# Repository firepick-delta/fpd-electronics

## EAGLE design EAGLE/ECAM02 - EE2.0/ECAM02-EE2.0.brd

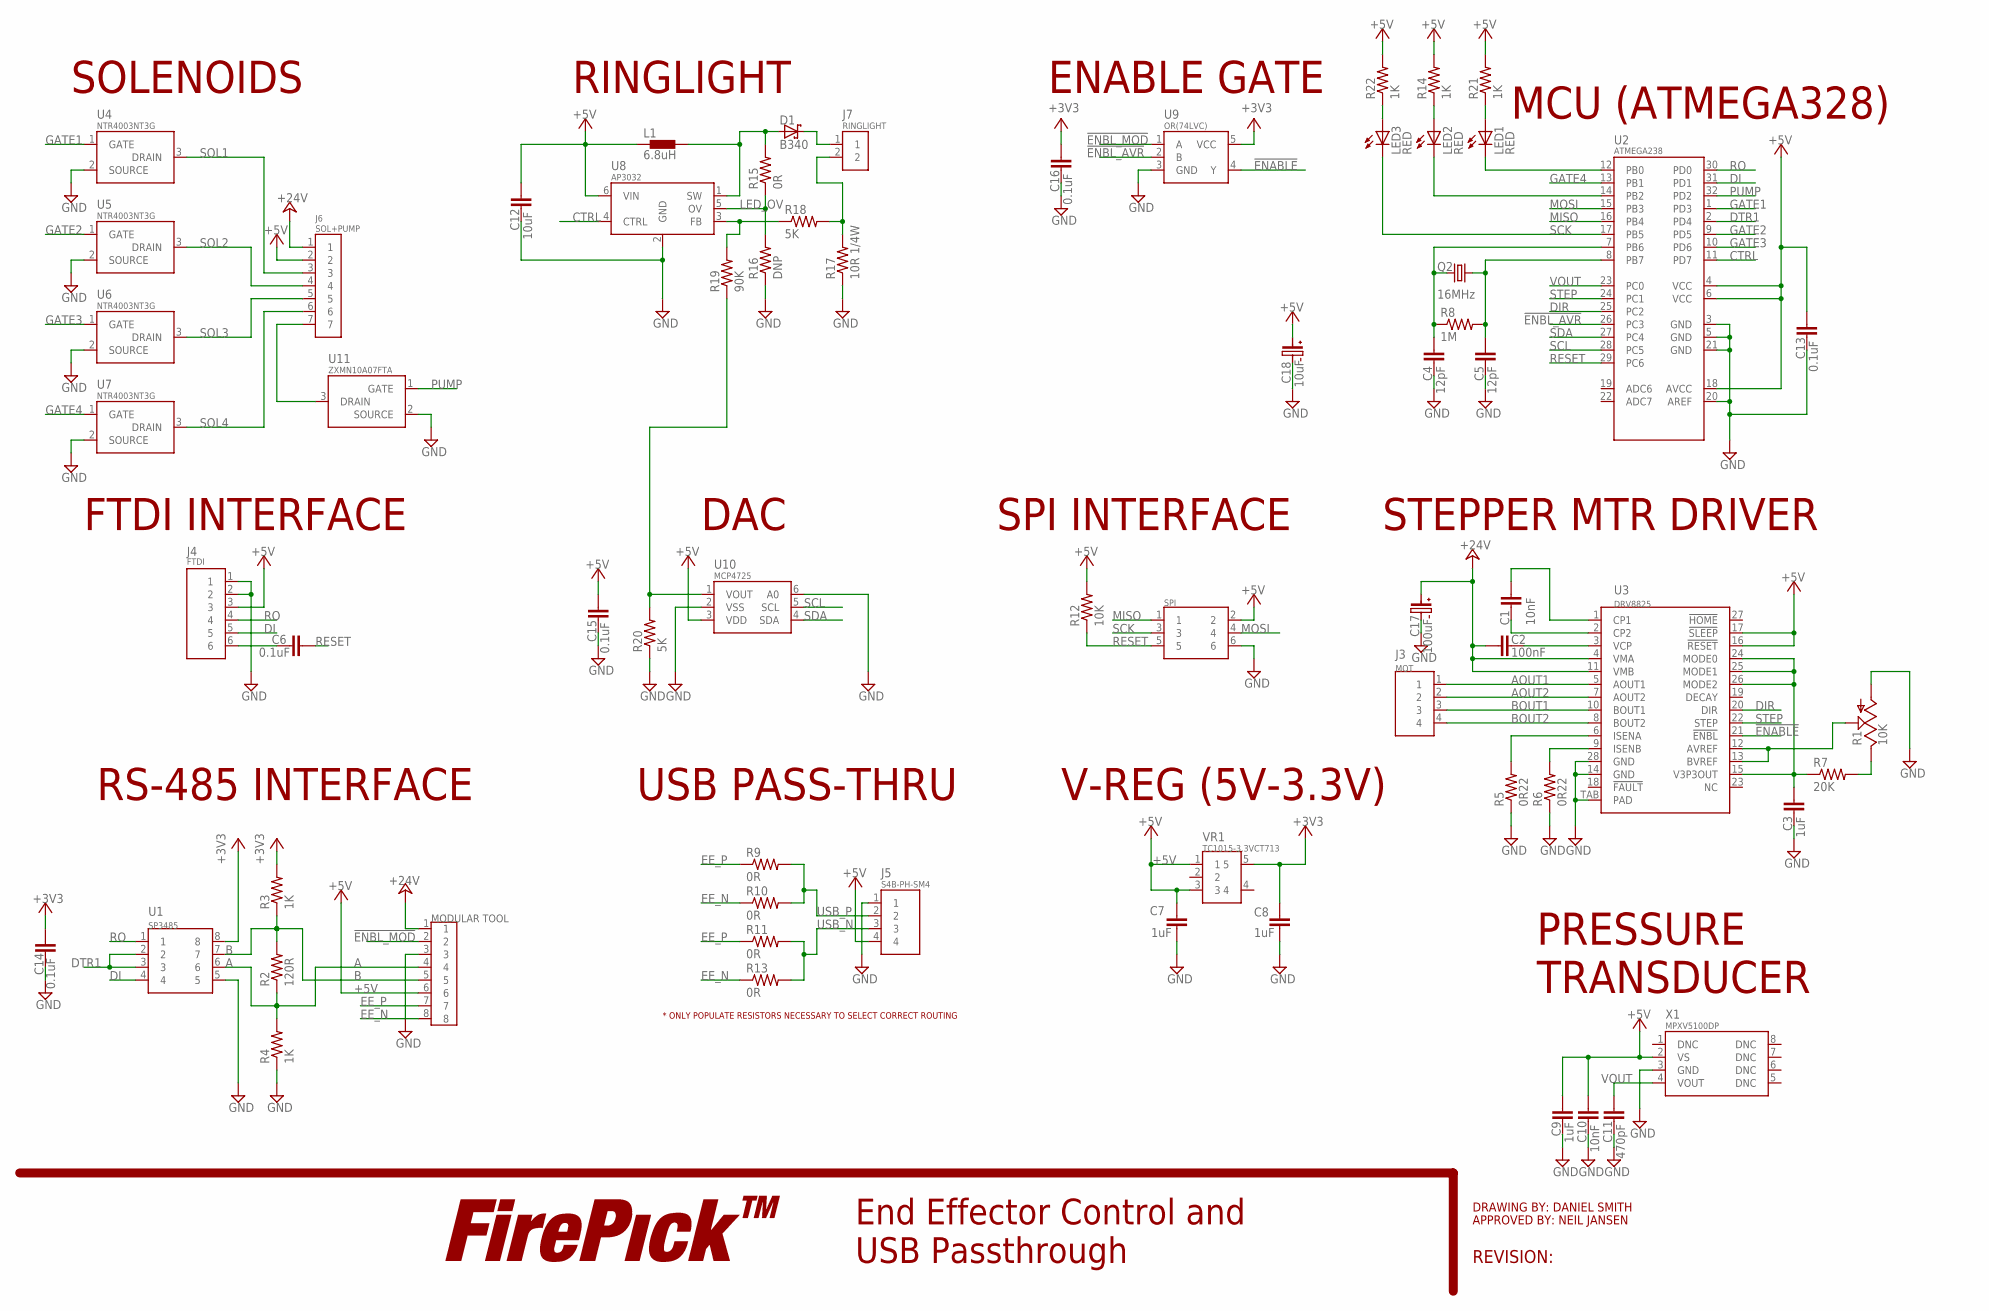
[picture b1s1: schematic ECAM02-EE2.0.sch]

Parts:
C1, C10: 10nF; C0603; PARTNO GRM188R71H103KA01D
C2: 100nF; C0603; PARTNO UMK107B7104KA-T
C3, C7, C8, C9: 1uF; C0603; PARTNO UMK107AB7105KA-T
C4, C5: 12pF; C0603; PARTNO GRM1885C1H120FA01J
C6: 0.1uF; C0603; PARTNO UMK107B7104KA-T
C11: 470pF; C0603; PARTNO GRM188R72A471KA01D
C12: 10uF; C0603; PARTNO GRM188R61C106MA73D
C13, C14, C15, C16: 0.1uF; C0603; PARTNO GMK107BJ104KAHT
C17: 100uF; C-SMD-6.3MM; PARTNO EMVA500ADA101MHA0G
C18: 10uF; C-SMD-6.3MM; PARTNO EMVH350ADA100MF60G
D1: B340; DIO-SMA; PARTNO B340A-13-F
J1: MODULAR TOOL; CON-JST-PH-2.0MM-8P-SMT-VRT; PARTNO B8B-PH-SM4-TB(LF)(SN)
J2: SPI; CON-HDR-2X3P; PARTNO 67996-206HLF
J3: MOT; CON-JST-PH-2.0MM-4P-THRU-VRT; PARTNO B4B-PH-K-S(LF)(SN)
J4: FTDI; CON-HDR-6POS-MALE; PARTNO S6B-PH-SM4-TB(LF)(SN)
J5: S4B-PH-SM4; CON-JST-PH-2.0MM-4P-SMT-VRT; PARTNO S4B-PH-SM4-TB(LF)(SN)
J6: SOL+PUMP; CON-JST-PH-2.0MM-7P-SMT-VRT; PARTNO B7B-PH-SM4-TB(LF)(SN)
J7: RINGLIGHT; CON-JST-PH-2.0MM-2P-SMT-VRT; PARTNO B2B-PH-SM4-TB(LF)(SN)
L1: 6.8uH; 0603; PARTNO BRL1608T6R8M
LED1, LED2, LED3: RED; LED0603
LOGO2: LOGO-FIREPICKLARGE; LOGO-FIREPICK
Q2: 16MHz; HC-49/U-S; PARTNO HCM4916000000ABJT
R1: 10K; TC33X-2; PARTNO TC33X-2-103E
R2: 120R; R0603; PARTNO RC0603FR-07120RL
R3, R4: 1K; R0603; PARTNO RC0603FR-071KL
R5, R6: 0R22; R1206; PARTNO RL1206FR-7W0R22L
R7: 20K; R0603; PARTNO RC0603FR-0722KL
R8: 1M; R0603; PARTNO RC0603FR-071ML
R9, R10, R11, R13, R15: 0R; R0603; PARTNO RC0603JR-070RL
R12: 10K; R0603; PARTNO RC0603FR-0710KL
R14, R21, R22: 1K; R0603
R16: DNP; R0603; PARTNO RC0603JR-070RL
R17: 10R 1/4W; R1206; PARTNO RC1206FR-0710RL
R18, R20: 5K; R0603; PARTNO PNM0603E5001BST5
R19: 90K; R0603; PARTNO RC0603FR-0790K9L
U1: SP3485; SOICN-8; PARTNO SP3485
U2: ATMEGA238; 32-TQF(ATMEGA); PARTNO ATMEGA328-AUR
U3: DRV8825; 28-HSSOP; PARTNO DRV8825PWPR
U4, U5, U6, U7: NTR4003NT3G; SOT-23-3; PARTNO NTR4003NT3G
U8: AP3032; SOT-23-6; PARTNO AP3032KTR-G1
U9: OR(74LVC); SOT-23-5; PARTNO SN74LVC1G32DBVR
U10: MCP4725; SOT-23-6; PARTNO MCP4725A0T-E/CH
U11: ZXMN10A07FTA; SOT-23-3; PARTNO ZXMN10A07FTA
VR1: TC1015-3.3VCT713; SOT-23-5; PARTNO TC1015-3.3VCT713
X1: MPXV5100DP; 8-SMD; PARTNO MPXV5100DP

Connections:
!ENABLE: U3.21 (!ENBL), U9.4 (Y)
!ENBL_AVR: U2.26 (PC3), U9.2 (B)
!ENBL_MOD: J1.2, U9.1 (A)
+3V3: C8.2, C14.2, C16.2, R3.2, U1.8, U9.5 (VCC), VR1.5
+5V: C7.2, C9.2, C10.2, C12.2, C13.2, C15.2, C18.POS, J1.6, J2.2, J4.3, J5.4, J6.2, L1.1, R12.2, R14.2, R21.2, R22.2, U2.4 (VCC), U2.6 (VCC), U2.18 (AVCC), U3.16 (!RESET), U3.17 (!SLEEP), U8.6 (VIN), U10.3 (VDD), VR1.1, VR1.3, X1.2 (VS)
+24V: C2.1, C17.POS, J1.1, J6.1, U3.4 (VMA), U3.11 (VMB)
A: J1.4, R2.1, R4.2, U1.6
AOUT1: J3.1, U3.5 (AOUT1)
AOUT2: J3.2, U3.7 (AOUT2)
B: J1.5, R2.2, R3.1, U1.7
BOUT1: J3.3, U3.10 (BOUT1)
BOUT2: J3.4, U3.8 (BOUT2)
CTRL: U2.11 (PD7), U8.4 (CTRL)
DI: J4.5, U1.4, U2.31 (PD1)
DIR: U2.25 (PC2), U3.20 (DIR)
DTR1: U1.2, U1.3, U2.2 (PD4)
EE_N: J1.8, R10.1, R13.1
EE_P: J1.7, R9.1, R11.1
GATE1: U2.1 (PD3), U4.1 (GATE)
GATE2: U2.9 (PD5), U5.1 (GATE)
GATE3: U2.10 (PD6), U6.1 (GATE)
GATE4: U2.13 (PB1), U7.1 (GATE)
GND: C3.1, C4.1, C5.1, C7.1, C8.1, C9.1, C10.1, C11.1, C12.1, C13.1, C14.1, C15.1, C16.1, C17.NEG, C18.NEG, J1.3, J2.6, J4.1, J4.2, J5.1, R1.1 (A), R4.1, R5.1, R6.1, R16.1, R17.1, R20.1, U1.5, U2.3 (GND), U2.5 (GND), U2.20 (AREF), U2.21 (GND), U3.14 (GND), U3.28 (GND), U3.TAB (PAD), U4.2 (SOURCE), U5.2 (SOURCE), U6.2 (SOURCE), U7.2 (SOURCE), U8.2 (GND), U9.3 (GND), U10.2 (VSS), U10.6 (A0), U11.2 (SOURCE), X1.3 (GND)
LED_ANODE: D1.NEG (C), J7.1
LED_CATHODE: J7.2, R17.2, R18.2
LED_FB: R18.1, R19.2, U8.3 (FB)
LED_OV: R15.1, R16.2, U8.5 (OV)
LED_SW: D1.POS (A), L1.2, R15.2, U8.1 (SW)
MISO: J2.1, U2.16 (PB4)
MOSI: J2.4, U2.15 (PB3)
unnamed: LED1.A, R21.1
unnamed: LED2.A, R14.1
unnamed: LED1.C, U2.12 (PB0)
unnamed: LED2.C, U2.14 (PB2)
unnamed: C1.2, U3.1 (CP1)
unnamed: C1.1, U3.2 (CP2)
unnamed: C2.2, U3.3 (VCP)
unnamed: R5.2, U3.6 (ISENA)
unnamed: R6.2, U3.9 (ISENB)
unnamed: R19.1, R20.2, U10.1 (VOUT)
unnamed: LED3.A, R22.1
unnamed: J6.7, U11.3 (DRAIN)
unnamed: C3.2, R7.1, U3.15 (V3P3OUT), U3.24 (MODE0), U3.25 (MODE1), U3.26 (MODE2)
unnamed: R1.3 (E), R7.2
unnamed: R1.2 (S), U3.12 (AVREF), U3.13 (BVREF)
unnamed: C6.1, J4.6
PUMP: U2.32 (PD2), U11.1 (GATE)
RESET: C6.2, J2.5, R12.1, U2.29 (PC6)
RO: J4.4, U1.1, U2.30 (PD0)
SCK: J2.3, LED3.C, U2.17 (PB5)
SCL: U2.28 (PC5), U10.5 (SCL)
SDA: U2.27 (PC4), U10.4 (SDA)
SOL1: J6.3, U4.3 (DRAIN)
SOL2: J6.4, U5.3 (DRAIN)
SOL3: J6.5, U6.3 (DRAIN)
SOL4: J6.6, U7.3 (DRAIN)
STEP: U2.24 (PC1), U3.22 (STEP)
USB_N: J5.3, R11.2, R13.2
USB_P: J5.2, R9.2, R10.2
VOUT: C11.2, U2.23 (PC0), X1.4 (VOUT)
XTAL1: C4.2, Q2.1, R8.1, U2.7 (PB6)
XTAL2: C5.2, Q2.2, R8.2, U2.8 (PB7)

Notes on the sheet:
End Effector Control and USB Passthrough
DRAWING BY: DANIEL SMITH
APPROVED BY: NEIL JANSEN
REVISION:
RS-485 INTERFACE
MCU (ATMEGA328)
V-REG (5V-3.3V)
FTDI INTERFACE
STEPPER MTR DRIVER
USB PASS-THRU
* ONLY POPULATE RESISTORS NECESSARY TO SELECT CORRECT ROUTING
PRESSURE TRANSDUCER
SOLENOIDS
RINGLIGHT
ENABLE GATE
DAC
SPI INTERFACE
SPI

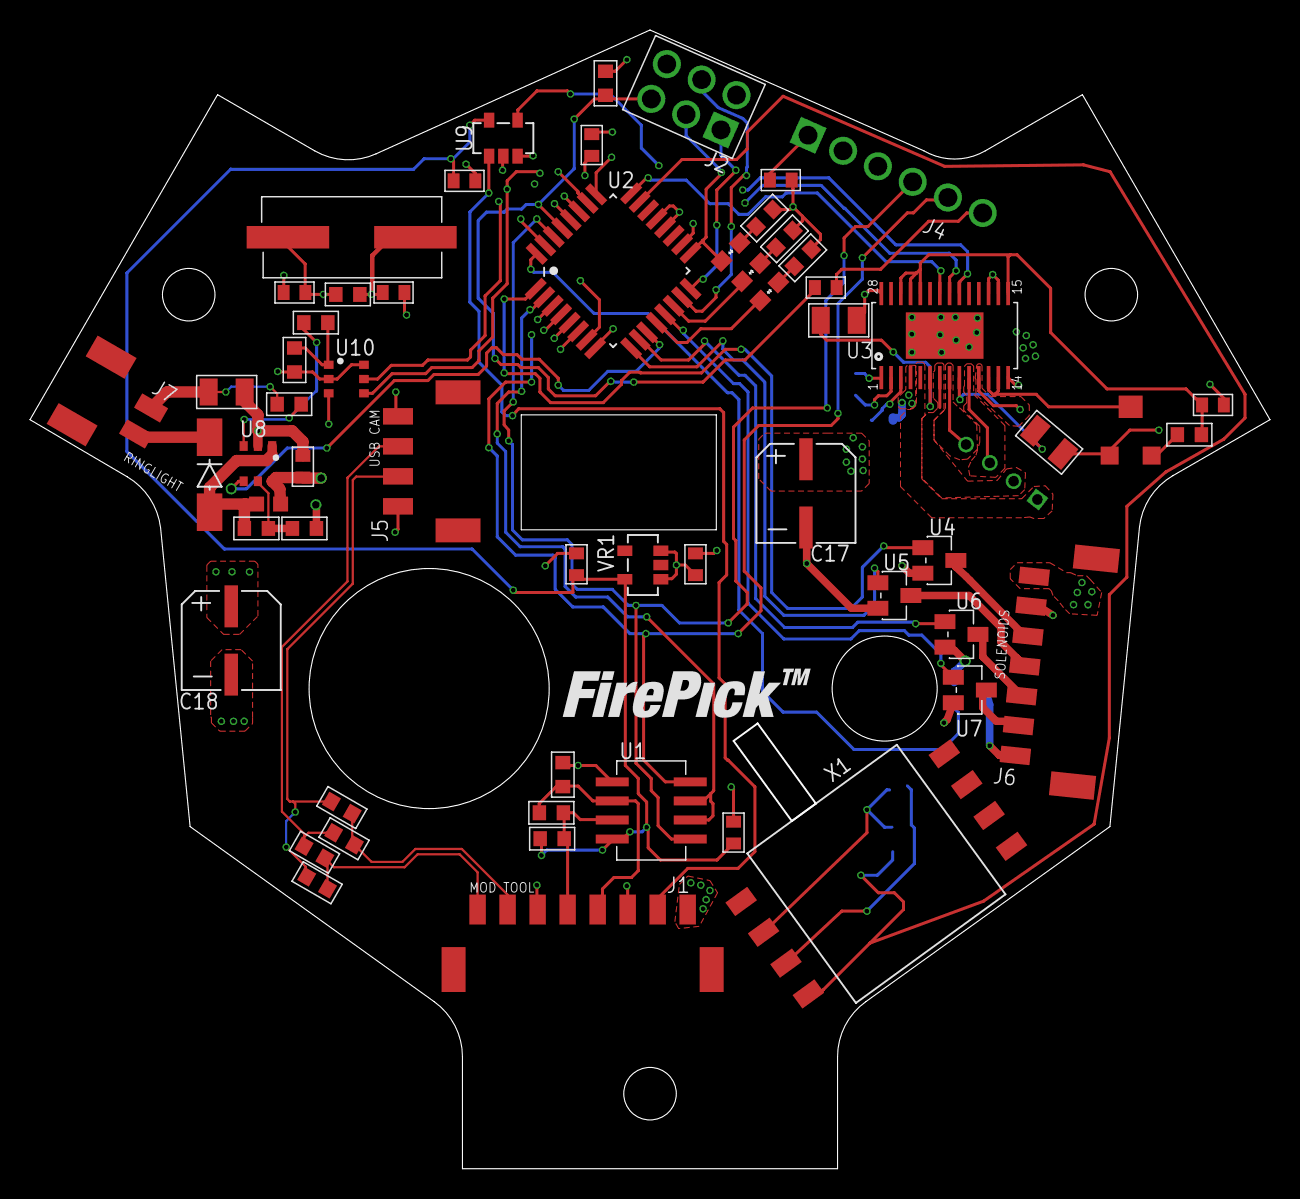
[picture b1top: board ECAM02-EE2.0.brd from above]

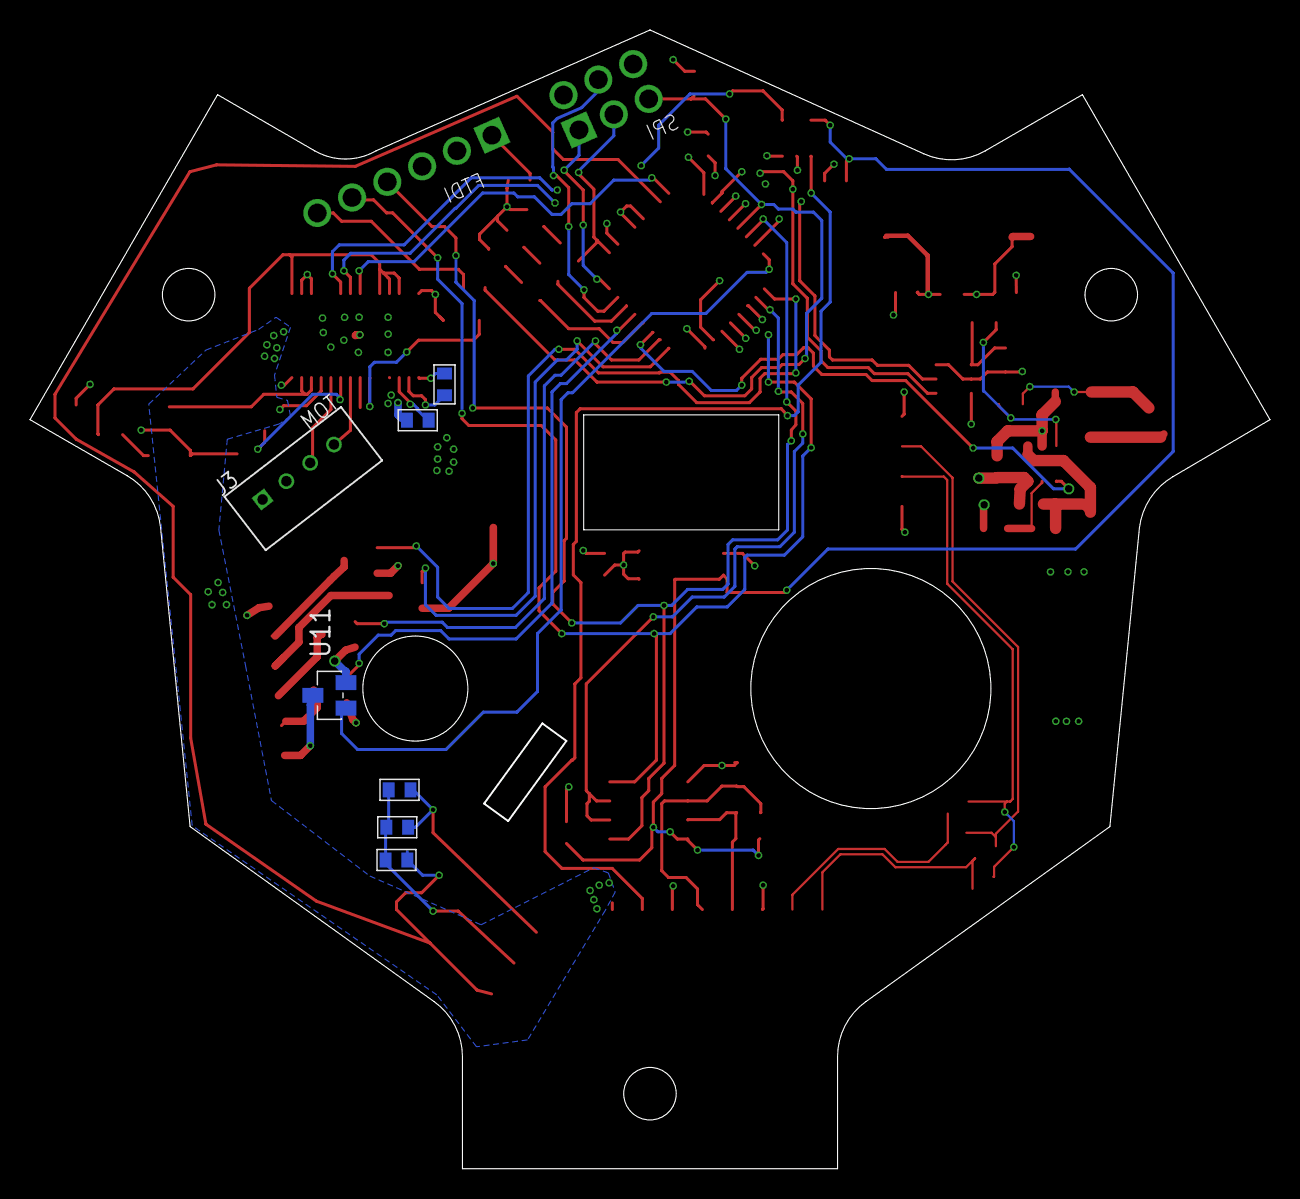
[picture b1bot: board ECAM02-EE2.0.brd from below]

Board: 4 copper layers, 82.5 x 75.8 mm, 67 parts (7 on the bottom side), 62 nets.

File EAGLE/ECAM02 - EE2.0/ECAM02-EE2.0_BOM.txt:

Mfg Part Num	Description	Qty-1	Part References	Price(USD):	Mfr:	Distr:	Digi-Key P/N:	Notes
ECAM02	End Effector & Downward Camera Board	-	ECAM02	-	Tin Whiskers Tech	-	-	
-	Bare PCB, FR-4, 0.062” Thickness	1	-		HQPCB	-	-	
GMK107BJ104KAHT	Capacitor: 0.1uF, 35V, 10%, X5R	4	C13, C14, C15, C16		Taiyo Yuden	ANY	587-3357-2-ND 	
UMK107B7104KA-T	Capacitor: 0.1uF, 50V, 10%, X7R	1	C6		Taiyo Yuden	ANY	587-1243-1-ND	
RC0603JR-070RL	Resistor: 0.0 Ohm, 0.1W, 0%	5	R9, R10, R11, R13, R15		Yageo	ANY	311-0.0GRCT-ND	
RL1206FR-7W0R22L	Resistor: 0.22 Ohm, 0.5W, 1%	2	R5, R6		Yageo	ANY	311-.22LYCT-ND	
RC0603FR-071KL	Resistor: 1 kOhm, 0.1W, 1%	2	R3, R4		Yageo	ANY	311-1.00KHRCT-ND	
RC0603FR-071ML	Resistor: 1 Mohm, 0.1W, 5%	1	R8		Yageo	ANY	311-1.00MHRCT-ND	
UMK107AB7105KA-T	Capacitor, 1uF, 50V, 10%	4	C3, C7, C8, C9		Taiyo Yuden	ANY	587-3247-1-ND	
PNM0603E5001BST5	Resistor: 5.0 kOhm, 0.1%, 0.15W	2	R18, R20		Vishay	ANY	PNM0603-5.0KBCT	
BRL1608T6R8M	Inductor: 6.8uH, 20%, SMT	1	L1		Taiyo Yuden	ANY	587-2902-1-ND	
RC0603FR-0710KL	Resistor: 10 kOhm, 0.1W, 1%	1	R12		Yageo	ANY	311-10.0KHRCT-ND	
TC33X-2-103E	Potentiometer: Trim, 10 kOhm, 0.1W, 25%	1	R1		Bourns Inc.	ANY	TC33X-103EDKR-ND	
RC1206FR-0710RL	Resistor: 10 Ohm, 0.25W, 1%	1	R17		Yageo	ANY	311-10.0FRCT-ND	
GRM188R71H103KA01D	Capacitor: 10nF, 50V, 10%, X7R	2	C1, C10		Murata	ANY	490-1512-1-ND	
EMVH350ADA100MF60G	Capacitor, AL-Electrolytic, 10uF, 35V, 20%	1	C18		United Chemi-Con	ANY	565-2310-2-ND	
GRM188R61C106MA73D	Capacitor: 10uF, 16V, 20%	1	C12		Murata	ANY	490-7201-1-ND	
GRM1885C1H120FA01J	Capacitor: 12pF, 50V, 1%, C0G	2	C4, C5		Murata	ANY	490-10705-1-ND	
HCM4916000000ABJT	Crystal Oscillator: 16MHz, 18pF, SMD	1	Q2		Citizen FM	ANY	300-6134-1-ND	
RC0603FR-0722KL	Resistor: 22 kOhm, 0.1W, 5%	1	R7		Yageo	ANY	311-22.0KHRCT-ND	
RC0603FR-0790K9L	Resistor: 90.9 kOhm, 0.1W, 1%	1	R19		Yageo	ANY	311-90.9KHRCT-ND	
RC0603FR-07100RL	Resistor: 100 Ohm, 0.1W, 1%	1	R2		Yageo	ANY	311-100HRCT-ND	
UMK107B7104KA-T	Capacitor: 0.1uF, 50V, 10%, X7R	1	C2		Taiyo Yuden	ANY	587-1243-1-ND	
EMVA500ADA101MHA0G	Capacitor, Al-Electrolytic, 100uF, 50V, 20%	1	C17		United Chemi-Con	ANY	565-2133-2-ND	
GRM188R72A471KA01D	Capacitor: 470pF, 100V, 10%, X7R	1	C11		Murata	ANY	490-1467-2-ND	
AP3032KTR-G1	Driver: LED, Regulator/Dimmer	1	U8		Diodes Incorporated	ANY	AP3032KTR-G1DICT-ND	
ATMEGA328-AUR	Microprocessor: AVR, 20MHz, 8-Bit Core	1	U2		Atmel	ANY	ATMEGA328-AURCT-ND	
B340A-13-F	Diode: Rectifier (Schottky), 3A, 40V	1	D1		Diodes Incorporated	ANY	FB340A-FDICT-ND	
RC0603JR-070RL	Resistor: 0.0 Ohm, 0.1W, 0%	1	R16		Yageo	ANY	311-0.0GRCT-ND	
DRV8825PWPR	Motor Driver: Bipolar, Stp/Dir, 1/32, 2.5A	1	U3		Texas Instruments	ANY	296-29503-1-ND	
S6B-PH-SM4-TB(LF)(SN)	Connector: 2.0mm (JST), SMT, R/A, 6-POS(M)	1	J4		JST	ANY	455-1753-1-ND	
MCP4725A0T-E/CH	DAC: 12BIT, I2C	1	U10		Microchip Tech.	ANY	MCP4725A0T-E/CHCT-ND	
B8B-PH-SM4-TB(LF)(SN)	Connector: 2.0mm (JST), SMT, VRT, 8-POS(M)	1	J1		JST	ANY	455-1740-1-ND	
S4B-PH-SM4-TB(LF)(SN)	Connector: 2.0mm (JST), SMT, R/A, 4-POS(M)	1	J3		JST	ANY	455-1751-1-ND	
MPXV5004GP	Sensor: Pressure, 0.57PSI, 5V	1	X1		Freescale Semi	ANY	MPXV5004GP-ND	
NTR4003NT3G	MOSFET: N-Ch, 30V, 500mA	5	U4, U5, U6, U7, U11		ON Semiconductor	ANY	NTR4003NT3GOSCT-ND	
SN74LVC1G32DBVR	Logic Gate: OR, 1-CH, SOT23-5	1	U9		Texas Instruments	ANY	296-9847-1-ND	
B2B-PH-SM4-TB(LF)(SN)	Connector: 2.0mm (JST), SMT, VRT, 2-POS(M)	1	J7		JST	ANY	455-1734-1-ND	
S4B-PH-SM4-TB(LF)(SN)	Connector: 2.0mm (JST), SMT, R/A, 4-POS(M)	1	J5		JST	ANY	455-1751-1-ND	
B7B-PH-SM4-TB(LF)(SN)	Connector: 2.0mm (JST), SMT, VRT, 7-POS(M)	1	J6		JST	ANY	455-1739-1-ND	
SP3485	Transceiver: RS-485 Chip	1	U1		EXAR	ANY	1016-1817-1-ND	
67996-206HLF	Connector: Header, 0.1ﾔ, 6-Pin, Male, Thru-Hole	1	J2		FCI	ANY	609-3210-ND	
TC1015-3.3VCT713	Voltage Reg(LDO): Vi=6V, Vo=3.3V, Io=0.1A	1	VR1		Microchip Tech.	ANY	TC1015-3.3VCT713CT-ND	
			TOTAL:

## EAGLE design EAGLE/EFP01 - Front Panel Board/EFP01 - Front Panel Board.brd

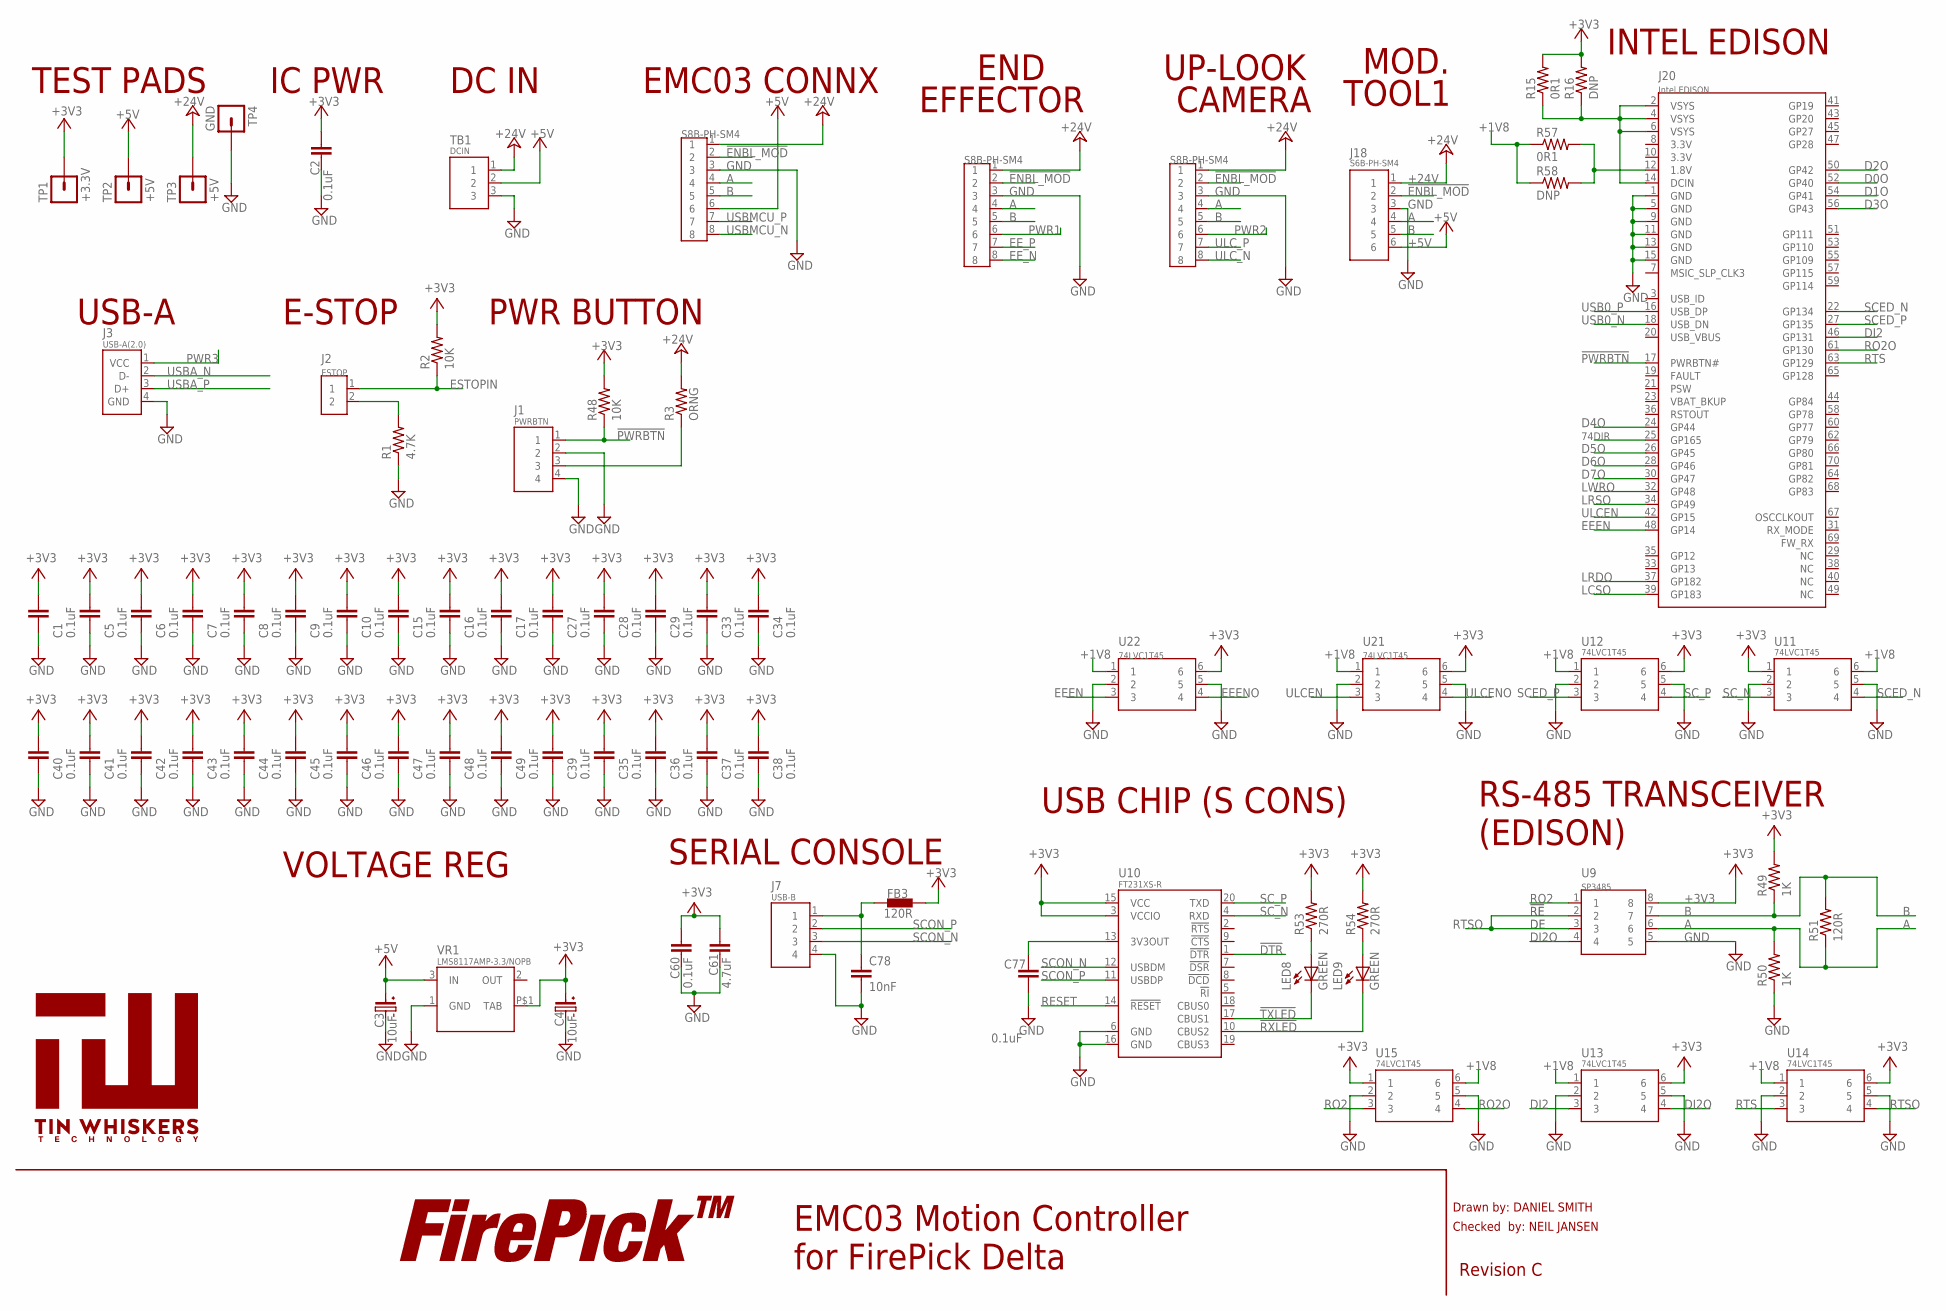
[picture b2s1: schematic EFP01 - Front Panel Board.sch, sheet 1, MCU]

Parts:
C1, C2, C5, C6, C7, C8, C9, C10, C15, C16, C17, C27, C28, C29, C33, C34, C35, C36, C37, C38, C39, C40, C41, C42, C43, C44, C45, C46, C47, C48, C49, C60, C77: 0.1uF; C0603; PARTNO GMK107BJ104KAHT
C3, C4: 10uF; C-SMD-6.3MM; PARTNO EMVH350ADA100MF60G
C61: 4.7uF; C0603; PARTNO GRM188C81E475KE11D
C78: 10nF; C0603; PARTNO GRM188R71H103KA01D
FB3: 120R; F0603; PARTNO BLM18AG121SN1D
J1: PWRBTN; CON-JST-PH-2.0MM-4P-SMT-VRT; PARTNO S4B-PH-SM4-TB(LF)(SN)
J2: ESTOP; CON-JST-PH-2.0MM-2P-SMT-VRT; PARTNO S2B-PH-SM4-TB(LF)(SN)
J3: USB-A(2.0); USB-A-THRU-VERT-2.0; PARTNO 1734085-1
J6, J16, J17: S8B-PH-SM4; CON-JST-PH-2.0MM-8P-SMT-VRT; PARTNO B8B-PH-SM4-TB(LF)(SN)
J7: USB-B; USB-B(SMT)-VERT-1734517; PARTNO 1734517-1
J18: S6B-PH-SM4; CON-JST-PH-2.00MM-6P-SMT-VRT; PARTNO B6B-PH-SM4-TB(LF)(SN)
J20: Intel EDISON; DF40HC(3.0)-70DS-0.4V(51); PARTNO DF40HC(3.0)-70DS-0.4V(51)
LED8, LED9: GREEN; LED0603; PARTNO SML-D12M8WT86
LOGO1: LOGO-FIREPICKLARGE; LOGO-FIREPICK
R1: 4.7K; R0603; PARTNO RC0603FR-074K7L
R2, R48: 10K; R0603; PARTNO RC0603FR-0710KL
R3: ORNG; R0603; PARTNO RC0603JR-070RL
R15, R57: 0R1; R0603; PARTNO RL0603FR-070R1L
R16, R58: DNP; R0603; PARTNO RC0603JR-070RL
R49, R50: 1K; R0603; PARTNO RC0603FR-071KL
R51: 120R; R0603; PARTNO RC0603FR-07120RL
R53, R54: 270R; R0603; PARTNO RC0603FR-07270RL
TB1: DCIN; TBLOCK-3-5MM-OSTTH030160; PARTNO OSTTH030160
TP1: +3.3V; TESTPAD; PARTNO N/A
TP2, TP3: +5V; TESTPAD; PARTNO N/A
TP4: GND; TESTPAD; PARTNO N/A
U9: SP3485; SOICN-8; PARTNO SP3485
U10: FT231XS-R; 20-SSOP; PARTNO FT231XS-R
U11, U12, U13, U14, U15, U21, U22: 74LVC1T45; SOT-363; PARTNO 74LVC1T45GW,125
U$1: TIN-WHISKERSTSTOP; TIN-WHISKERS-TSTOP; PARTNO *
VR1: LMS8117AMP-3.3/NOPB; SOT-223; PARTNO LMS8117AMP-3.3/NOPB

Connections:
74DIR: J20.25 (GP165); also elsewhere on the board
!DTR: U10.1 (!DTR)
!ENBL_MOD: J6.2, J16.2, J17.2, J18.2
!PWRBTN: J1.1, J20.17 (PWRBTN#), R48.1
!RXLED: LED9.C, U10.10 (CBUS2)
!TXLED: LED8.C, U10.17 (CBUS1)
+1V8: R57.1, R58.1, U11.6, U12.1, U13.1, U14.1, U15.6, U21.1, U22.1; also elsewhere on the board
+3V3: C1.2, C2.2, C4.POS, C5.2, C6.2, C7.2, C8.2, C9.2, C10.2, C15.2, C16.2, C17.2, C27.2, C28.2, C29.2, C33.2, C34.2, C35.2, C36.2, C37.2, C38.2, C39.2, C40.2, C41.2, C42.2, C43.2, C44.2, C45.2, C46.2, C47.2, C48.2, C49.2, C60.2, C61.2, FB3.2, R2.2, R15.2, R16.2, R48.2, R49.2, R53.2, R54.2, TP1.PAD, U9.8, U10.3 (VCCIO), U10.15 (VCC), U11.1, U12.6, U13.6, U14.6, U15.1, U21.6, U22.6, VR1.P$1 (TAB); also elsewhere on the board
+5V: C3.POS, J6.6, J18.6, TB1.2, TP2.PAD, VR1.3 (IN); also elsewhere on the board
+24V: J6.1, J16.1, J17.1, J18.1, R3.2, TB1.1, TP3.PAD
A: J6.4, J16.4, J17.4, J18.4, R50.2, R51.1, U9.6
B: J6.5, J16.5, J17.5, J18.5, R49.1, R51.2, U9.7
D0O: J20.52 (GP40); also elsewhere on the board
D1O: J20.54 (GP41); also elsewhere on the board
D2O: J20.50 (GP42); also elsewhere on the board
D3O: J20.56 (GP43); also elsewhere on the board
D4O: J20.24 (GP44); also elsewhere on the board
D5O: J20.26 (GP45); also elsewhere on the board
D6O: J20.28 (GP46); also elsewhere on the board
D7O: J20.30 (GP47); also elsewhere on the board
DI2: J20.46 (GP131), U13.3
DI2O: U9.4, U13.4
EEEN: J20.48 (GP14), U22.3
EEENO: U22.4; also elsewhere on the board
EE_N: J16.8; also elsewhere on the board
EE_P: J16.7; also elsewhere on the board
ESTOPIN: J2.1, R2.1
GND: C1.1, C2.1, C3.NEG, C4.NEG, C5.1, C6.1, C7.1, C8.1, C9.1, C10.1, C15.1, C16.1, C17.1, C27.1, C28.1, C29.1, C33.1, C34.1, C35.1, C36.1, C37.1, C38.1, C39.1, C40.1, C41.1, C42.1, C43.1, C44.1, C45.1, C46.1, C47.1, C48.1, C49.1, C60.1, C61.1, C77.1, C78.1, J1.2, J1.4, J3.4 (GND), J6.3, J7.4, J16.3, J17.3, J18.3, J20.1 (GND), J20.5 (GND), J20.9 (GND), J20.11 (GND), J20.13 (GND), J20.15 (GND), R1.1, R50.1, TB1.3, TP4.PAD, U9.5, U10.6 (GND), U10.16 (GND), U11.2, U11.5, U12.2, U12.5, U13.2, U13.5, U14.2, U14.5, U15.2, U15.5, U21.2, U21.5, U22.2, U22.5, VR1.1 (GND); also elsewhere on the board
LCSO: J20.39 (GP183); also elsewhere on the board
LRDO: J20.37 (GP182); also elsewhere on the board
LRSO: J20.34 (GP49); also elsewhere on the board
LWRO: J20.32 (GP48); also elsewhere on the board
unnamed: C77.2, U10.13 (3V3OUT)
unnamed: C78.2, FB3.1, J7.1
unnamed: J1.3, R3.1
unnamed: J2.2, R1.2
unnamed: LED9.A, R54.1
unnamed: LED8.A, R53.1
unnamed: J20.12 (1.8V), R57.2, R58.2
unnamed: J20.2 (VSYS), J20.4 (VSYS), J20.6 (VSYS), J20.14 (DCIN), R15.1, R16.1
PWR1: J16.6; also elsewhere on the board
PWR2: J17.6; also elsewhere on the board
PWR3: J3.1 (VCC); also elsewhere on the board
RESET: U10.14 (!RESET)
RO2: U9.1, U15.3
RO2O: J20.61 (GP130), U15.4
RTS: J20.63 (GP129), U14.3
RTSO: U9.2, U9.3, U14.4
SCED_N: J20.22 (GP134), U11.4
SCED_P: J20.27 (GP135), U12.3
SCON_N: J7.3, U10.12 (USBDM)
SCON_P: J7.2, U10.11 (USBDP)
SC_N: U10.4 (RXD), U11.3
SC_P: U10.20 (TXD), U12.4
ULCEN: J20.42 (GP15), U21.3
ULCENO: U21.4; also elsewhere on the board
ULC_N: J17.8; also elsewhere on the board
ULC_P: J17.7; also elsewhere on the board
USB0_N: J20.18 (USB_DN); also elsewhere on the board
USB0_P: J20.16 (USB_DP); also elsewhere on the board
USBA_N: J3.2 (D-); also elsewhere on the board
USBA_P: J3.3 (D+); also elsewhere on the board
USBMCU_N: J6.8; also elsewhere on the board
USBMCU_P: J6.7; also elsewhere on the board

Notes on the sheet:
Drawn by: DANIEL SMITH
Checked by: NEIL JANSEN
Revision C
EMC03 Motion Controller for FirePick Delta
!RE
RS-485 TRANSCEIVER
(EDISON)
PWR BUTTON
SERIAL CONSOLE
INTEL EDISON
USB CHIP (S CONS)
E-STOP
TEST PADS
IC PWR
END
EFFECTOR
MOD.
TOOL1
UP-LOOK
CAMERA
DC IN
USB-A
EMC03 CONNX
VOLTAGE REG

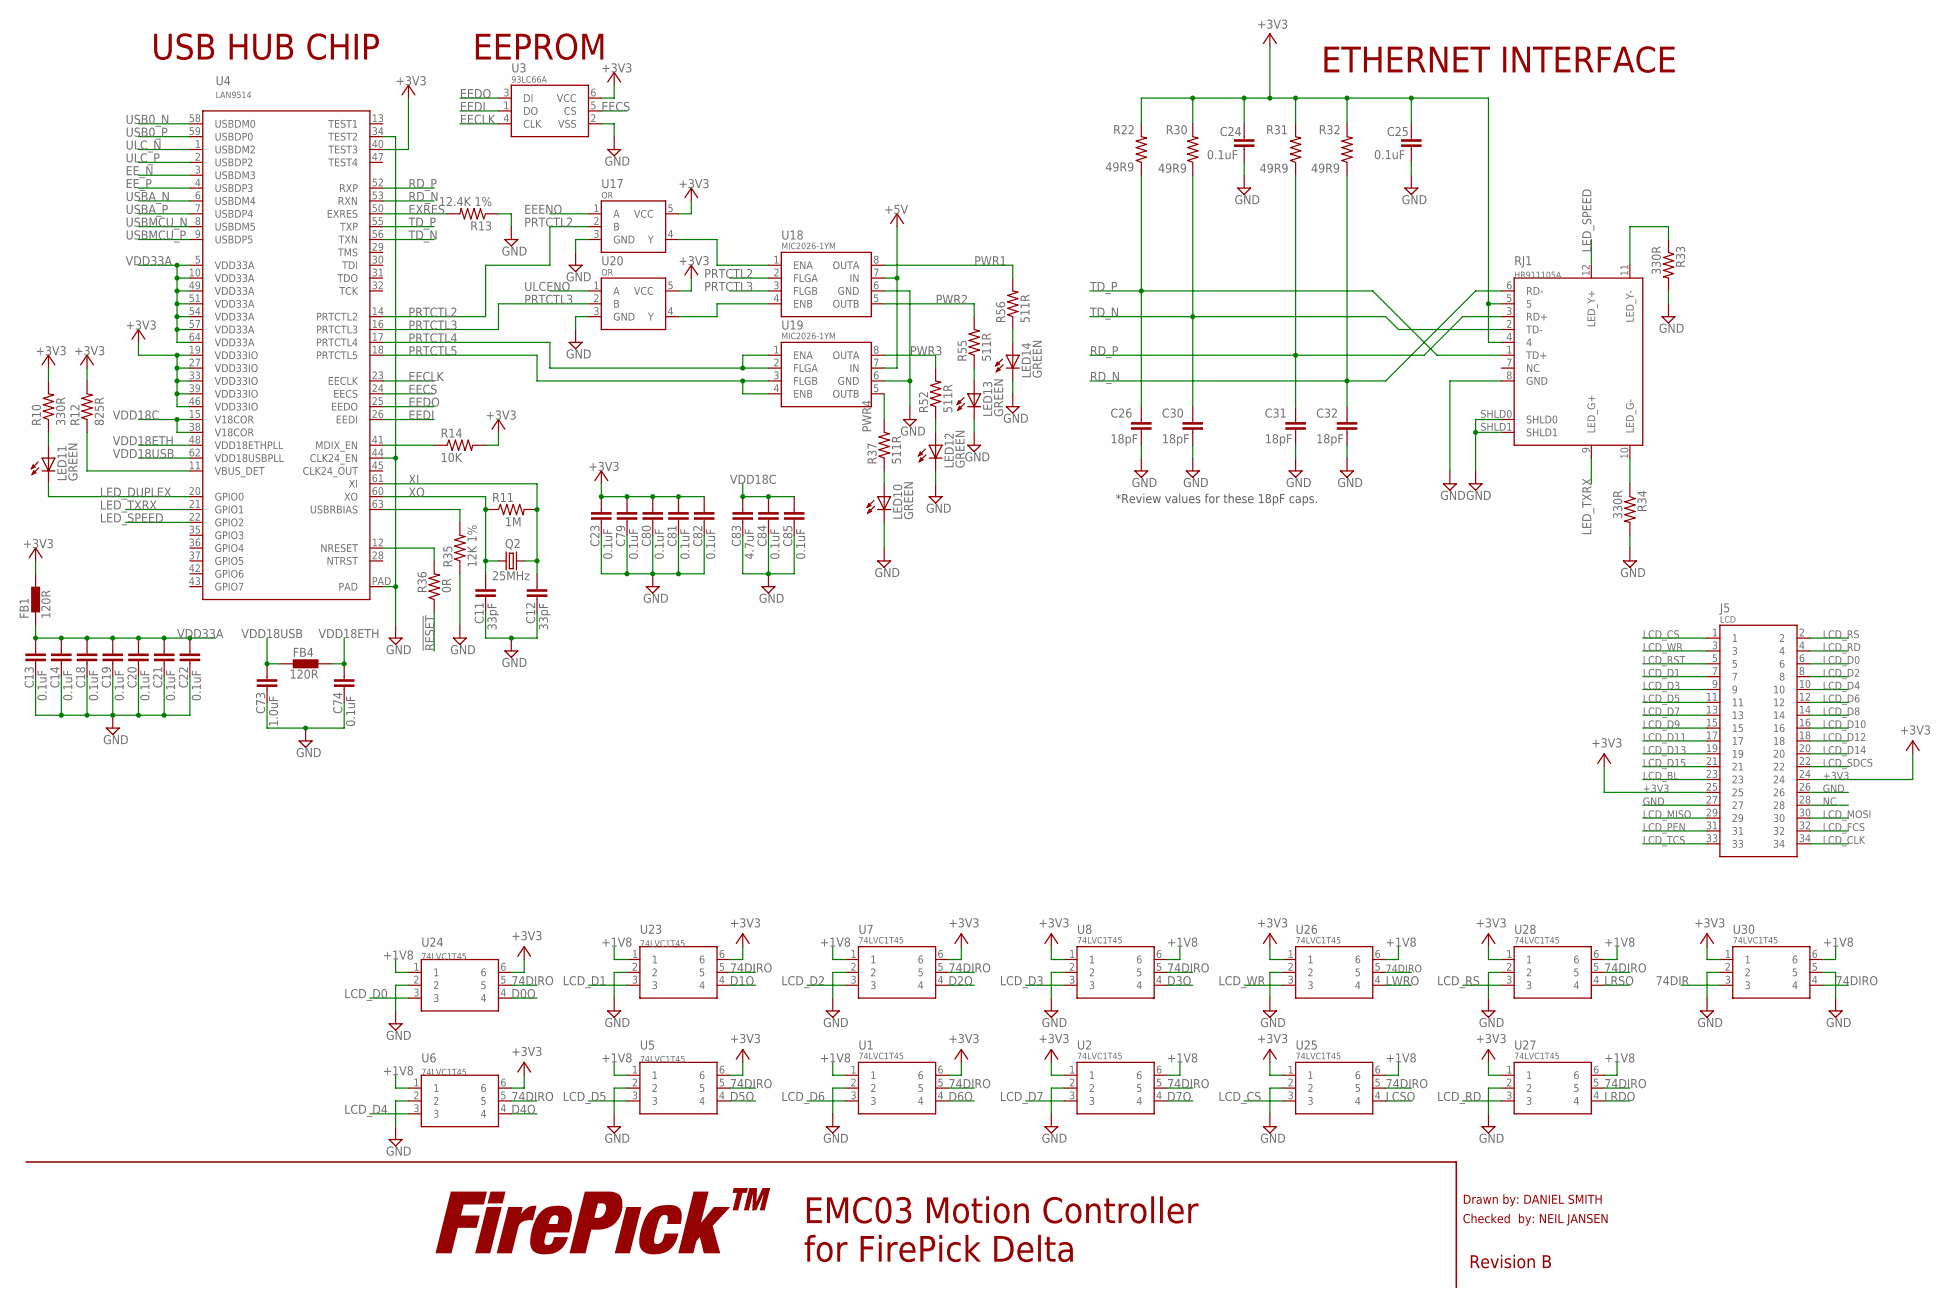
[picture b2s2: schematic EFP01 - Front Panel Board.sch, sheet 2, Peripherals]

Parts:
C11, C12: 33pF; C0603; PARTNO C0603C330K5GACTU
C13, C14, C18, C19, C20, C21, C22, C23, C24, C25, C74, C79, C80, C81, C82, C84, C85: 0.1uF; C0603; PARTNO GMK107BJ104KAHT
C26, C30, C31, C32: 18pF; C0603; PARTNO GCM1885C1H180JA16D
C73: 1.0uF; C0603; PARTNO UMK107AB7105KA-T
C83: 4.7uF; C0603; PARTNO GRM188C81E475KE11D
FB1, FB4: 120R; F0603; PARTNO BLM18AG121SN1D
J5: LCD; LCD-34P-3.2IN; PARTNO TSW-117-07-T-D
LED10, LED11, LED12, LED13, LED14: GREEN; LED0603; PARTNO SML-D12M8WT86
LOGO2: LOGO-FIREPICKLARGE; LOGO-FIREPICK
Q2: 25MHz; HC-49/U-S; PARTNO HCM4925000000MABJ
R10, R33, R34: 330R; R0603; PARTNO RC0603FR-07330RL
R11: 1M; R0603; PARTNO RC0603FR-071ML
R12: 825R; R0603; PARTNO RC0603FR-07825RL
R13: 12.4K 1%; R0603; PARTNO RC0603FR-0712K4L
R14: 10K; R0603; PARTNO RC0603FR-0710KL
R22, R30, R31, R32: 49R9; R0603; PARTNO RC0603FR-0749R9L
R35: 12K 1%; R0603; PARTNO RC0603FR-0712KL
R36: 0R; R0603; PARTNO RC0603JR-070RL
R37, R52, R55, R56: 511R; R0603; PARTNO RC0603FR-07511RL
RJ1: HR911105A; MAGJACK(HR911105A); PARTNO HR911105A
U1, U2, U5, U6, U7, U8, U23, U24, U25, U26, U27, U28, U30: 74LVC1T45; SOT-363; PARTNO 74LVC1T45GW,125
U3: 93LC66A; SOT-23-6; PARTNO 93LC66A-I/SN
U4: LAN9514; 64-QFN; PARTNO LAN9514-JZX
U17, U20: OR; SOT-23-5; PARTNO SN74LVC1G32DBVR
U18, U19: MIC2026-1YM; SOIC-8; PARTNO MIC2026-1YM

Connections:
74DIR: U30.3; also elsewhere on the board
74DIRO: U1.5, U2.5, U5.5, U6.5, U7.5, U8.5, U23.5, U24.5, U25.5, U26.5, U27.5, U28.5, U30.4
!RESET: R36.1
+1V8: U1.1, U2.6, U5.1, U6.1, U7.1, U8.6, U23.1, U24.1, U25.6, U26.6, U27.6, U28.6, U30.6; also elsewhere on the board
+3V3: C23.2, C24.2, C25.2, C79.2, C80.2, C81.2, C82.2, FB1.2, J5.24, J5.25, R10.2, R12.2, R14.2, R22.2, R30.2, R31.2, R32.2, RJ1.4, RJ1.5, U1.6, U2.1, U3.6 (VCC), U4.19 (VDD33IO), U4.27 (VDD33IO), U4.33 (VDD33IO), U4.39 (VDD33IO), U4.40 (TEST3), U4.46 (VDD33IO), U5.6, U6.6, U7.6, U8.1, U17.5 (VCC), U20.5 (VCC), U23.6, U24.6, U25.1, U26.1, U27.1, U28.1, U30.1; also elsewhere on the board
+5V: U18.7 (IN), U19.7 (IN); also elsewhere on the board
D0O: U24.4; also elsewhere on the board
D1O: U23.4; also elsewhere on the board
D2O: U7.4; also elsewhere on the board
D3O: U8.4; also elsewhere on the board
D4O: U6.4; also elsewhere on the board
D5O: U5.4; also elsewhere on the board
D6O: U1.4; also elsewhere on the board
D7O: U2.4; also elsewhere on the board
EECLK: U3.4 (CLK), U4.23 (EECLK)
EECS: U3.5 (CS), U4.24 (EECS)
EEDI: U3.1 (DO), U4.26 (EEDI)
EEDO: U3.3 (DI), U4.25 (EEDO)
EEENO: U17.1 (A); also elsewhere on the board
EE_N: U4.3 (USBDM3); also elsewhere on the board
EE_P: U4.4 (USBDP3); also elsewhere on the board
EXRES: R13.2, U4.50 (EXRES)
GND: C11.1, C12.1, C13.1, C14.1, C18.1, C19.1, C20.1, C21.1, C22.1, C23.1, C24.1, C25.1, C26.1, C30.1, C31.1, C32.1, C73.1, C74.1, C79.1, C80.1, C81.1, C82.1, C83.1, C84.1, C85.1, J5.26, J5.27, LED10.C, LED12.C, LED13.C, LED14.C, R13.1, R33.2, R34.2, R35.1, RJ1.8 (GND), RJ1.SHLD0, RJ1.SHLD1, U1.2, U2.2, U3.2 (VSS), U4.34 (TEST2), U4.44 (CLK24_EN), U4.PAD, U5.2, U6.2, U7.2, U8.2, U17.3 (GND), U18.6 (GND), U19.6 (GND), U20.3 (GND), U23.2, U24.2, U25.2, U26.2, U27.2, U28.2, U30.2, U30.5; also elsewhere on the board
LCD_BL: J5.23
LCD_CLK: J5.34
LCD_CS: J5.1, U25.3
LCD_D0: J5.6, U24.3
LCD_D1: J5.7, U23.3
LCD_D2: J5.8, U7.3
LCD_D3: J5.9, U8.3
LCD_D4: J5.10, U6.3
LCD_D5: J5.11, U5.3
LCD_D6: J5.12, U1.3
LCD_D7: J5.13, U2.3
LCD_D8: J5.14
LCD_D9: J5.15
LCD_D10: J5.16
LCD_D11: J5.17
LCD_D12: J5.18
LCD_D13: J5.19
LCD_D14: J5.20
LCD_D15: J5.21
LCD_FCS: J5.32
LCD_MISO: J5.29
LCD_MOSI: J5.30
LCD_PEN: J5.31
LCD_RD: J5.4, U27.3
LCD_RS: J5.2, U28.3
LCD_RST: J5.5
LCD_SDCS: J5.22
LCD_TCS: J5.33
LCD_WR: J5.3, U26.3
LCSO: U25.4; also elsewhere on the board
LED_DUPLEX: LED11.C, U4.20 (GPIO0)
LED_SPEED: RJ1.12 (LED_Y+), U4.22 (GPIO2)
LED_TXRX: RJ1.9 (LED_G+), U4.21 (GPIO1)
LRDO: U27.4; also elsewhere on the board
LRSO: U28.4; also elsewhere on the board
LWRO: U26.4; also elsewhere on the board
unnamed: LED11.A, R10.1
unnamed: R12.1, U4.11 (VBUS_DET)
unnamed: R33.1, RJ1.11 (LED_Y-)
unnamed: R34.1, RJ1.10 (LED_G-)
unnamed: R36.2, U4.12 (NRESET)
unnamed: R14.1, U4.41 (MDIX_EN)
unnamed: U17.4 (Y), U18.1 (ENA)
unnamed: R35.2, U4.63 (USBRBIAS)
unnamed: LED10.A, R37.1
unnamed: LED12.A, R52.1
unnamed: LED13.A, R55.1
unnamed: LED14.A, R56.1
unnamed: U18.4 (ENB), U20.4 (Y)
NC: J5.28
PRTCTL2: U4.14 (PRTCTL2), U17.2 (B), U18.2 (FLGA)
PRTCTL3: U4.16 (PRTCTL3), U18.3 (FLGB), U20.2 (B)
PRTCTL4: U4.17 (PRTCTL4), U19.1 (ENA), U19.2 (FLGA)
PRTCTL5: U4.18 (PRTCTL5), U19.3 (FLGB), U19.4 (ENB)
PWR1: R56.2, U18.8 (OUTA); also elsewhere on the board
PWR2: R55.2, U18.5 (OUTB); also elsewhere on the board
PWR3: R52.2, U19.8 (OUTA); also elsewhere on the board
PWR4: R37.2, U19.5 (OUTB)
RD_N: C32.2, R32.1, RJ1.6 (RD-), U4.53 (RXN)
RD_P: C31.2, R31.1, RJ1.3 (RD+), U4.52 (RXP)
TD_N: C30.2, R30.1, RJ1.2 (TD-), U4.56 (TXN)
TD_P: C26.2, R22.1, RJ1.1 (TD+), U4.55 (TXP)
ULCENO: U20.1 (A); also elsewhere on the board
ULC_N: U4.1 (USBDM2); also elsewhere on the board
ULC_P: U4.2 (USBDP2); also elsewhere on the board
USB0_N: U4.58 (USBDM0); also elsewhere on the board
USB0_P: U4.59 (USBDP0); also elsewhere on the board
USBA_N: U4.6 (USBDM4); also elsewhere on the board
USBA_P: U4.7 (USBDP4); also elsewhere on the board
USBMCU_N: U4.8 (USBDM5); also elsewhere on the board
USBMCU_P: U4.9 (USBDP5); also elsewhere on the board
VDD18C: C83.2, C84.2, C85.2, U4.15 (V18COR), U4.38 (V18COR)
VDD18ETH: C74.2, FB4.2, U4.48 (VDD18ETHPLL)
VDD18USB: C73.2, FB4.1, U4.62 (VDD18USBPLL)
VDD33A: C13.2, C14.2, C18.2, C19.2, C20.2, C21.2, C22.2, FB1.1, U4.5 (VDD33A), U4.10 (VDD33A), U4.49 (VDD33A), U4.51 (VDD33A), U4.54 (VDD33A), U4.57 (VDD33A), U4.64 (VDD33A)
XI: C12.2, Q2.2, R11.2, U4.61 (XI)
XO: C11.2, Q2.1, R11.1, U4.60 (XO)

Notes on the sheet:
Drawn by: DANIEL SMITH
Checked by: NEIL JANSEN
Revision B
EMC03 Motion Controller for FirePick Delta
*Review values for these 18pF caps.
ETHERNET INTERFACE
EEPROM
USB HUB CHIP

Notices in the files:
parts and their libraries:
SparkFun-Aesthetics: Licensing: Creative Commons ShareAlike 4.0 International - https://creativecommons.org/licenses/by-sa/4.0
